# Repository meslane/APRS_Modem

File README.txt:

_       _     _ _ _     _      _     _    _     _ _ _
/\_\    /\_\  /\_\_\_\  /\_\ _ /\_\  /\_\ /\_\  /\_\_\_\
\/\_\   \ \_\ \/\_\/_/_ \/\_\_\\_\_\ \/\_\__\_\ \/\_\/\_\
 \/\_\  _\ \_\ \/\_\_\_\ \/\_\//\_\_\ \/_/_\_\/_ \/\_\_\_\
  \/\_\/\_\_\_\ \/\_\/\_\ \/\_\\/_/\_\  /\ \_/\ \ \/\_\/_/
   \/\_\_\_\_\_\ \/\_\_\_\ \/\_\  \/\_\ \/\_\\/\_\ \/\_\ 
    \/_/_/_/_/_/  \/_/_/_/  \/_/   \/_/  \/_/ \/_/  \/_/
    
 ##   ###   ###    ###    #   #   ##   ###   ####  #   #  #
#  #  #  #  #  #  #       ## ##  #  #  #  #  #     ## ##  #
####  ###   ###    ##     # # #  #  #  #  #  ####  # # #  #
#  #  #     # #      #    #   #  #  #  #  #  #     #   #  
#  #  #     #  #  ###     #   #   ##   ###   ####  #   #  #

~== Current Functionality ==~
-Encoding and transmission of arbitrary packets over resistor DAC
-Automatic radio push-to-talk activation
-GPS module support
-LCD + rotart encoder user interface
-Persistent settings
-TX jitter setting
-RX capabilites + decoding + CRC checking
-Python TX/RX script

~== Tips and Tricks ==~
-Make sure you're not over/under-driving the output of the transmit circuit.
 Over/under modulation can cause a reciever to fail to properly decode packets.
 You should test this with a second radio and the python demodulation script included here
-Also check reciever volume into your PC for the same reasons
 The demodulator is more resistant to distortion than noise, but it can't hurt

~== Current Bugs (TOFIX) ==~
-AGC on the reciever looks like it may require a longer start/stop flag to lock on
	-Will need to test further though

~== Acknowlegements ==~
-Cal EE123 (packet formatting info): https://inst.eecs.berkeley.edu/~ee123/sp15/lab/lab6/Lab6_Part_B-APRS.html
-Matthew Tran (verification code): https://matthewtran.dev/
-UCR CS120B for LCD code
-Mark Adler on StackOverflow for CRC function code

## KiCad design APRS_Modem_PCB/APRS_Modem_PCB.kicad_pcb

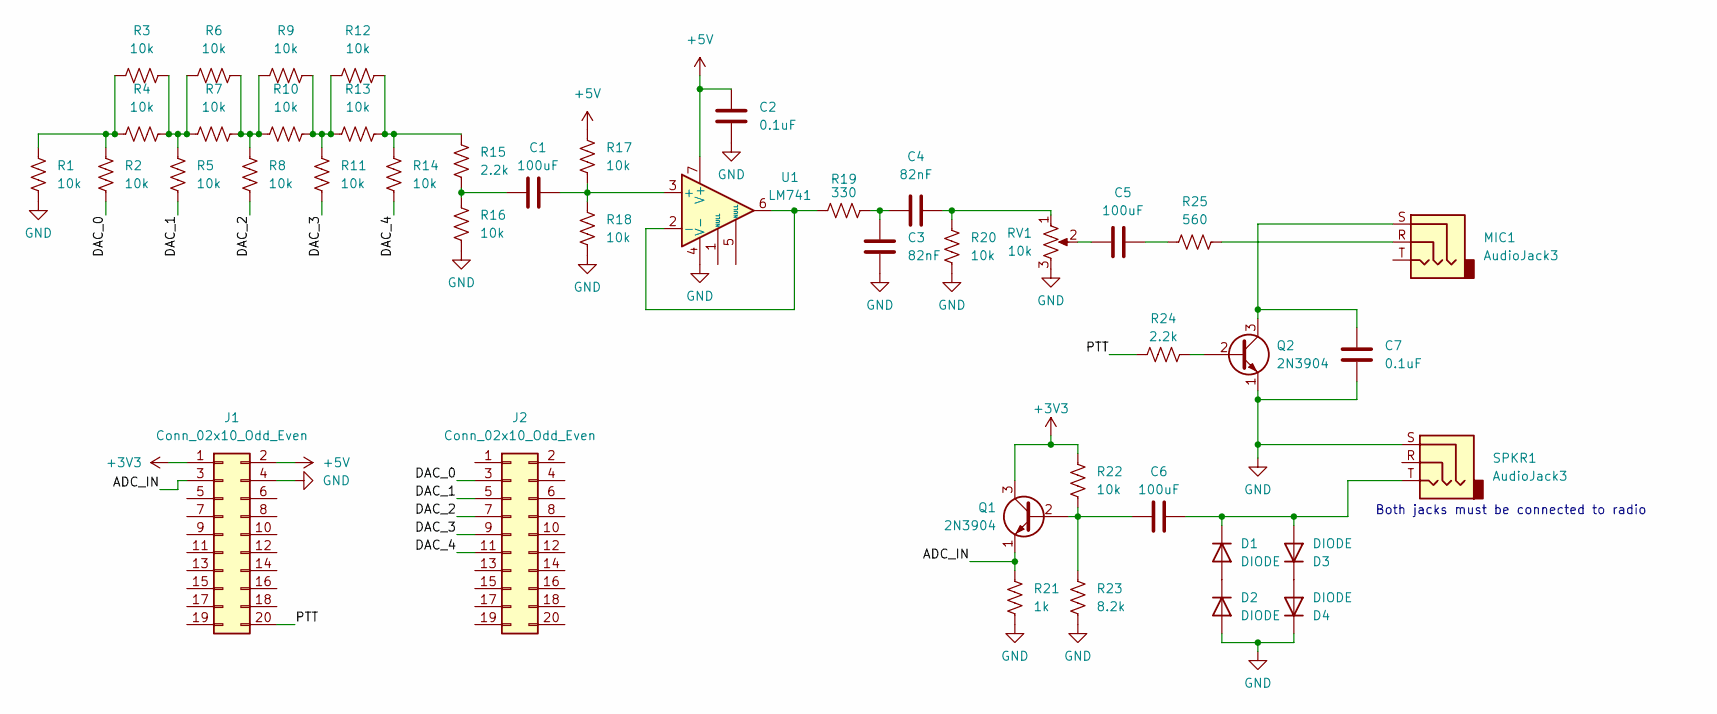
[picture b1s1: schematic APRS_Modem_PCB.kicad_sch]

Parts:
C1, C5, C6: 100uF; CP_Radial_D8.0mm_P3.80mm
C2, C7: 0.1uF; C_Disc_D4.3mm_W1.9mm_P5.00mm
C3, C4: 82nF; C_Disc_D4.3mm_W1.9mm_P5.00mm
D1, D2, D3, D4: DIODE; D_A-405_P7.62mm_Horizontal
J1, J2: Conn_02x10_Odd_Even; PinHeader_2x10_P2.54mm_Vertical
MIC1: AudioJack3; Jack_3.5mm_CUI_SJ1-3525N_Horizontal
Q1, Q2: 2N3904; TO-92_Inline
R1, R3, R4, R6, R7, R9, R10, R12, R13: 10k; R_Axial_DIN0207_L6.3mm_D2.5mm_P5.08mm_Vertical
R2, R5, R8, R11, R14, R16, R17, R18, R20, R22: 10k; R_Axial_DIN0207_L6.3mm_D2.5mm_P10.16mm_Horizontal
R15, R24: 2.2k; R_Axial_DIN0207_L6.3mm_D2.5mm_P10.16mm_Horizontal
R19: 330; R_Axial_DIN0207_L6.3mm_D2.5mm_P10.16mm_Horizontal
R21: 1k; R_Axial_DIN0207_L6.3mm_D2.5mm_P10.16mm_Horizontal
R23: 8.2k; R_Axial_DIN0207_L6.3mm_D2.5mm_P10.16mm_Horizontal
R25: 560; R_Axial_DIN0207_L6.3mm_D2.5mm_P10.16mm_Horizontal
RV1: 10k; Potentiometer_Alpha_RD901F-40-00D_Single_Vertical
SPKR1: AudioJack3; Jack_3.5mm_CUI_SJ1-3525N_Horizontal
U1: LM741; DIP-8_W7.62mm_LongPads

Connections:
+3V3: J1.1, Q1.3 (C), R22.1
+5V: C2.1, J1.2, R17.1, U1.7 (V+)
/ADC_IN: J1.3, Q1.1 (E), R21.1
/DAC_0: J2.3, R2.2
/DAC_1: J2.5, R5.2
/DAC_2: J2.7, R8.2
/DAC_3: J2.9, R11.2
/DAC_4: J2.11, R14.2
/PTT: J1.20, R24.1
GND: C2.2, C3.2, C7.2, D2.1 (A), D4.2 (K), J1.4, Q2.1 (E), R1.2, R16.2, R18.2, R20.2, R21.2, R23.2, RV1.3, SPKR1.S, U1.4 (V-)
unnamed: C1.1, R15.2, R16.1
unnamed: C1.2, R17.2, R18.1, U1.3 (+)
unnamed: D1.1 (A), D2.2 (K)
unnamed: C6.2, D1.2 (K), D3.1 (A), SPKR1.T
unnamed: D3.2 (K), D4.1 (A)
unnamed: MIC1.R, R25.2
unnamed: C7.1, MIC1.S, Q2.3 (C)
unnamed: C6.1, Q1.2 (B), R22.2, R23.1
unnamed: Q2.2 (B), R24.2
unnamed: R1.1, R2.1, R3.1, R4.1
unnamed: R3.2, R4.2, R5.1, R6.1, R7.1
unnamed: R6.2, R7.2, R8.1, R9.1, R10.1
unnamed: R9.2, R10.2, R11.1, R12.1, R13.1
unnamed: R12.2, R13.2, R14.1, R15.1
unnamed: C3.1, C4.1, R19.2
unnamed: C4.2, R20.1, RV1.1
unnamed: C5.2, R25.1
unnamed: C5.1, RV1.2
unnamed: R19.1, U1.2 (-), U1.6

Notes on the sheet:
Both jacks must be connected to radio

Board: 2 copper layers, 44 parts (0 on the bottom side), 29 nets, no tracks yet.

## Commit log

2023-04-12 first commit!
2023-04-15 make phase coherant and start packet forming
2023-04-16 saving just in case
2023-04-16 implement packet forming
2023-04-17 Now able to send decodable packets!
2023-04-17 add README + some fixes to dsp stuff
2023-04-18 add circuit schematics
2023-04-18 update schematic
2023-04-18 refactored code + fixed packet errors
2023-04-19 add push to talk
2023-04-19 can link to APRS network reliably
2023-04-20 update readme and remove useless code
2023-04-20 got GPS module working and tracking
2023-04-21 update readme + hopefully fix small bug
2023-04-21 integrate GPS and radio code into state machine
2023-04-25 start UI code
2023-04-25 more UI code
2023-04-25 small UI changes
2023-04-25 finish UI functionality
2023-04-26 add persistent settings and jitter
2023-05-02 last commit before final project demo
2023-05-15 add python scripts for demodulation
2023-05-15 able to demodulate from audio to NRZI
2023-05-16 add fixed point and hardware multiplication to MSP430 */
2023-05-17 improve fixed point math and update filters
2023-05-17 frequency comparator works!
2023-05-17 Muntz'd PLL code to the point where I think it can be ported
2023-05-17 PLL works!
2023-05-18 now decoded to NRZI stream
2023-05-18 basic working state
2023-05-18 can now demod arbitrary messages
2023-05-19 fixed extra byte issue and got RX CRC working
2023-05-21 start PCB schematic
2023-05-21 closed loop test works
2023-05-22 start PCB
2023-05-29 my own python modulator program works!
2023-05-29 remove prints
2023-05-29 can demod to packet data in python now
2023-05-29 have it demodulating, but CRC check is still wonky
2023-05-30 fixed passing CRC issue?
2023-05-30 single program Python modem works!
2023-05-30 update code + README
2023-05-30 update APRS display formatting in Python script
2023-06-01 got TX/RX loop with BBS working
2023-06-02 add struct message class
2023-06-02 have basic BBS functionality
2023-06-04 end-to-end communication over two baofengs works!
2023-06-05 add code from last night that I FORGOT
2023-06-05 this code doesn't work, committing to save it
2023-06-05 think the bug is it running out of RAM and not telling me
2023-06-05 full-ish functionality!
2023-06-05 now officially fully functional
2023-06-05 add tic-tac-toe, nearly complete
2023-06-06 Tic-Tac-Toe fully functional!
2023-06-06 minor changes to BBS
2023-06-06 final* commit before demos
2023-07-04 remove test file
